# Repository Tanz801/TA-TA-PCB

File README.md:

This is a PCB based on TA-TA from the game Arknight endfields. Designed to be a simple digital pet. This was made for week 1 of hackclub half-life, and I choose to make TA-TA because the beginner project was a digital pet and I just thought TA-TA was a pretty cool and cute character.

## Features

OLED screen for faces
Temperature sensor
Buzzer
Onboard battery charger
IMU to detect movement and orientation.

To be added:
Full organic feeling reactions to external stimuli

## Firmware flashing
The firmware can be flashed by downloading the firmware folder, opening as an esp-idf project, and flashing. However if you don't have the esp-idf framework installed or don't know how to use it, you can use python to flash the precompiled binaries through esptool

1. Install esptool``` pip install esptool ```
2. navigate to TA-TA-Firmware
3. run the following command
```python -m esptool --port PORT --baud 460800 write_flash @build/flashing_args```
replace PORT with the COM number of the esp if you're on windows, or the port on mac or linux.

## Assembling

Components just need to be soldered onto the pcb. The following sections can be done in any order:

### Microcontroller:
The Xiao ESP32 C3 is soldered onto the only component spot with surface mounts, the "pins" of the MCU should match the SMD pads on the PCB and the silkscreen

### Power button:
Solder the push button in the correct orientation based on the silkscreen at SW1, right side of the PCB

### Temperature sensor
Put the THT pins of the TMP36 through the holes next to U1 at the top left of the PCB, and bend it and solder it according to the silk screen.

A 0.1uF ceramic capacitor should be soldered at C1 directly underneath the TMP36

### IMU
If the MPU6050 did not come with header pins, solder headerpins onto the breakout board, make sure the spacers are at the bottom.
Solder the pins to J2 on the left of the microcontroller

### Buzzer
Solder the diode at D1, at the top of the PCB, make sure the direction of the diode (the white line) matches that of the silk screen

The transistor is soldered at the 3 THT holes at Q1, make sure the emitter is soldered to pin 1, the only hole among the 3 with a square pad.

A 1k resistor is soldered at R1, right below the transistor

Finally solder the buzzer at BZ1, with the anode at pin one (the hole with the square pad)

### Battery
the battery shouldn't be soldered but instead secured through any means such as double sided tape.
before connecting the battery to the jst connector, confirm the polarity of the battery, **look from the orientation where the buzzer would be at the top**. If when plugged in, the voltage source is on the right and gnd is on the left, nothing needs to be done, if its the reverse, scratch off the 2 preconnected solder jumpers at the bottom of the PCB then join the 2 previously disconnected jumpers with solder. Now the battery can be safely plugged in.

## BOM

|Item                                      |amount|cost (ea. CAD)|Link                                                                                                                                                                                                                                                                                                                                                                                                                                                                                                                                                                                                                                                                             |
|------------------------------------------|------|--------------|---------------------------------------------------------------------------------------------------------------------------------------------------------------------------------------------------------------------------------------------------------------------------------------------------------------------------------------------------------------------------------------------------------------------------------------------------------------------------------------------------------------------------------------------------------------------------------------------------------------------------------------------------------------------------------|
|XIAO ESP32 C3                             |1     |13.19         |https://www.aliexpress.com/item/1005008791937363.html?spm=a2g0o.productlist.main.1.a1e51039rrC4SW&algo_pvid=b22ce7b4-fbff-4a97-8525-81d1d1d06f15&algo_exp_id=b22ce7b4-fbff-4a97-8525-81d1d1d06f15-0&pdp_ext_f=%7B%22order%22%3A%221499%22%2C%22spu_best_type%22%3A%22price%22%2C%22eval%22%3A%221%22%2C%22fromPage%22%3A%22search%22%7D&pdp_npi=6%40dis%21CAD%2113.19%2113.19%21%21%219.07%219.07%21%402101ef5e17917414181325465e0fbf%2112000052930246748%21sea%21CA%213968153684%21X%211%210%21n_tag%3A-29919%3Bd%3Ab9e668a9%3Bm03_new_user%3A-29895&curPageLogUid=pBK0H0wVxh6J&utparam-url=scene%3Asearch%7Cquery_from%3A%7Cx_object_id%3A1005008791937363%7C_p_origin_prod%3A |
|0.96 OLED                                 |1     |3.86          |https://www.aliexpress.com/item/1005006141235306.html                                                                                                                                                                                                                                                                                                                                                                                                                                                                                                                                                                                                                            |
|MPU6050                                   |1     |3.41          |https://www.aliexpress.com/item/1005008714169630.html                                                                                                                                                                                                                                                                                                                                                                                                                                                                                                                                                                                                                            |
|TMP32 Temperature sensor                  |1     |0.92          |https://www.aliexpress.com/item/4000082221164.html?mp=1                                                                                                                                                                                                                                                                                                                                                                                                                                                                                                                                                                                                                          |
|Passive buzzer                            |1     |0.43          |https://www.aliexpress.com/item/1005006135620280.html?spm=a2g0o.productlist.main.1.73593b6a9n0rFF&algo_pvid=2a9f04ca-f1d5-416f-93e7-f65157e7bf2e&algo_exp_id=2a9f04ca-f1d5-416f-93e7-f65157e7bf2e-0&pdp_ext_f=%7B%22order%22%3A%22151%22%2C%22spu_best_type%22%3A%22price%22%2C%22eval%22%3A%221%22%2C%22fromPage%22%3A%22search%22%7D&pdp_npi=6%40dis%21CAD%216.52%214.25%21%21%2130.05%2119.60%21%402101ea8f17917437858606267e0c2c%2112000035917873697%21sea%21CA%213968153684%21X%211%210%21n_tag%3A-29919%3Bd%3Ab9e668a9%3Bm03_new_user%3A-29895&curPageLogUid=UEYBK5cUuoOp&utparam-url=scene%3Asearch%7Cquery_from%3A%7Cx_object_id%3A1005006135620280%7C_p_origin_prod%3A  |
|2N2222 NPN transistor                     |1     |0.09          |https://www.aliexpress.com/item/1005005776372882.html                                                                                                                                                                                                                                                                                                                                                                                                                                                                                                                                                                                                                            |
|300mAh LiPo Battery 3.7V                  |1     |8.79          |https://www.aliexpress.com/item/1005008218024646.html?spm=a2g0o.productlist.main.3.3e222b94krLFEf&algo_pvid=362b0e01-9ad2-44a0-9ac8-8f41d8200535&algo_exp_id=362b0e01-9ad2-44a0-9ac8-8f41d8200535-2&pdp_ext_f=%7B%22order%22%3A%228081%22%2C%22spu_best_type%22%3A%22price%22%2C%22eval%22%3A%221%22%2C%22fromPage%22%3A%22search%22%7D&pdp_npi=6%40dis%21CAD%2117.95%218.43%21%21%2182.69%2138.86%21%402101d3fe17917661419256252e1338%2112000044269020516%21sea%21CA%213968153684%21X%211%210%21n_tag%3A-29919%3Bd%3Ab9e668a9%3Bm03_new_user%3A-29895&curPageLogUid=c0LEzqcbYYwl&utparam-url=scene%3Asearch%7Cquery_from%3A%7Cx_object_id%3A1005008218024646%7C_p_origin_prod%3A|
|1N4148 Diodes                             |1     |0.02          |https://www.aliexpress.com/item/4001126137167.html?algo_exp_id=5643a195-8cb6-4ff1-847c-ea78bd3a77c7-1&pdp_ext_f=%7B%22order%22%3A%222192%22%2C%22spu_best_type%22%3A%22price%22%2C%22eval%22%3A%221%22%2C%22fromPage%22%3A%22search%22%7D&utparam-url=scene%3Asearch%7Cquery_from%3A%7Cx_object_id%3A4001126137167%7C_p_origin_prod%3A                                                                                                                                                                                                                                                                                                                                           |
|1k resistor                               |1     |0.01          |https://www.aliexpress.com/item/1005006186890215.html?mp=1                                                                                                                                                                                                                                                                                                                                                                                                                                                                                                                                                                                                                       |
| 0.1 µF ceramic capacitor                 |1     |0.02          |https://www.aliexpress.com/item/1005011742959553.html                                                                                                                                                                                                                                                                                                                                                                                                                                                                                                                                                                                                                            |
|JST-PH housing                            |1     |0.03          |https://www.aliexpress.com/item/1005004955655144.html?mp=1                                                                                                                                                                                                                                                                                                                                                                                                                                                                                                                                                                                                                       |
|6x6x5MM 4PIN G90 Tactile Tact Push Button |1     |0.06          |https://www.aliexpress.com/item/32873398324.html?mp=1&pdp_ext_f=%7B%22cart2PdpParams%22%3A%7B%22pdpBusinessMode%22%3A%22retail%22%7D%7D                                                                                                                                                                                                                                                                                                                                                                                                                                                                                                                                          |
|PCB                                       |1     |2.56          |https://cart.jlcpcb.com/quote?rand=0.883814583740498                                                                                                                                                                                                                                                                                                                                                                                                                                                                                                                                                                                                                             |
|Total                                     |      |33.39         |                     

## PCB Wiring and Schematics

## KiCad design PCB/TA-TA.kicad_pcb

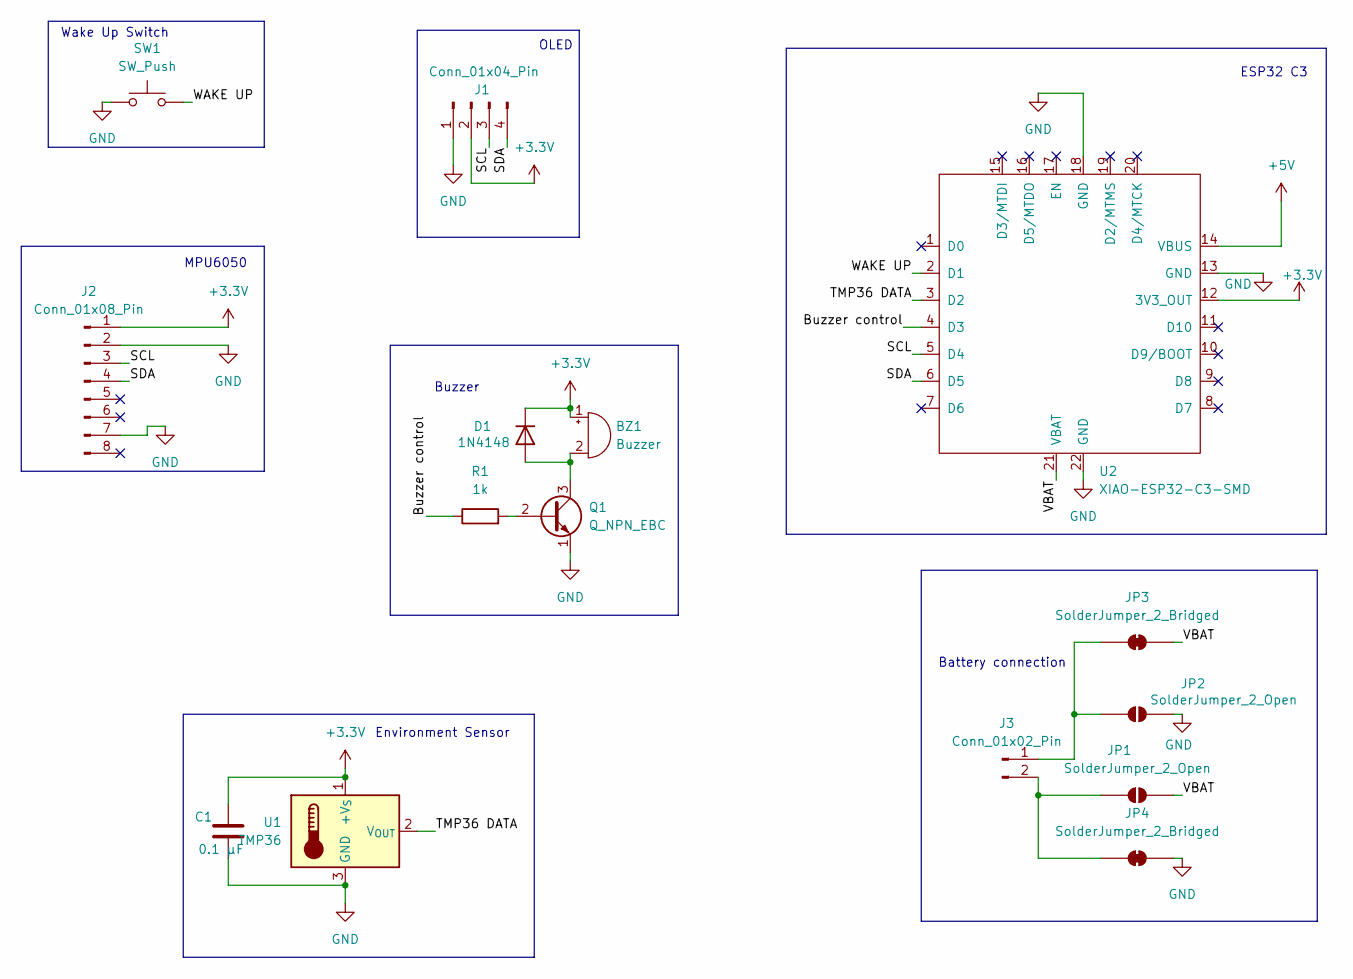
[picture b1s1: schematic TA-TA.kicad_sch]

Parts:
BZ1: Buzzer; Buzzer_12x9.5RM7.6
C1: 0.1 µF; C_Disc_D5.0mm_W2.5mm_P2.50mm
D1: 1N4148; D_DO-35_SOD27_P7.62mm_Horizontal
J1: Conn_01x04_Pin; Display_128x64_096_I2C
J2: Conn_01x08_Pin; MPU6050_Module
J3: Conn_01x02_Pin; JST_PH_S2B-PH-K_1x02_P2.00mm_Horizontal
JP1, JP2: SolderJumper_2_Open; SolderJumper-2_P1.3mm_Open_RoundedPad1.0x1.5mm
JP3, JP4: SolderJumper_2_Bridged; SolderJumper-2_P1.3mm_Bridged_RoundedPad1.0x1.5mm
Q1: Q_NPN_EBC; TO-92_Inline_W4.0mm_Horizontal_FlatSideDown
R1: 1k; R_Axial_DIN0207_L6.3mm_D2.5mm_P10.16mm_Horizontal
SW1: SW_Push; SW_PUSH_6mm
U1: TMP36; TO-92_W4.0mm_StaggerEven_Horizontal_FlatSideDown
U2: XIAO-ESP32-C3-SMD

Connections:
+3.3V: BZ1.1 (+), C1.1, D1.1 (K), J1.2, J2.1, U1.1 (+V_{S}), U2.12 (3V3_OUT)
+5V: U2.14 (VBUS)
/Buzzer control: R1.1, U2.4 (D3)
/SCL: J1.3, J2.3, U2.5 (D4)
/SDA: J1.4, J2.4, U2.6 (D5)
/TMP36 DATA: U1.2 (V_{OUT}), U2.3 (D2)
/VBAT: JP1.2 (B), JP3.2 (B), U2.21 (VBAT)
/WAKE UP: SW1.2, U2.2 (D1)
GND: C1.2, J1.1, J2.2, J2.7, JP2.2 (B), JP4.2 (B), Q1.1 (E), SW1.1, U1.3 (GND), U2.13 (GND), U2.18 (GND), U2.22 (GND)
unnamed: BZ1.2 (-), D1.2 (A), Q1.3 (C)
unnamed: J3.1, JP2.1 (A), JP3.1 (A)
unnamed: J3.2, JP1.1 (A), JP4.1 (A)
unnamed: Q1.2 (B), R1.2

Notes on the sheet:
Environment Sensor
ESP32 C3
OLED
Battery connection
Wake Up Switch
Buzzer
MPU6050

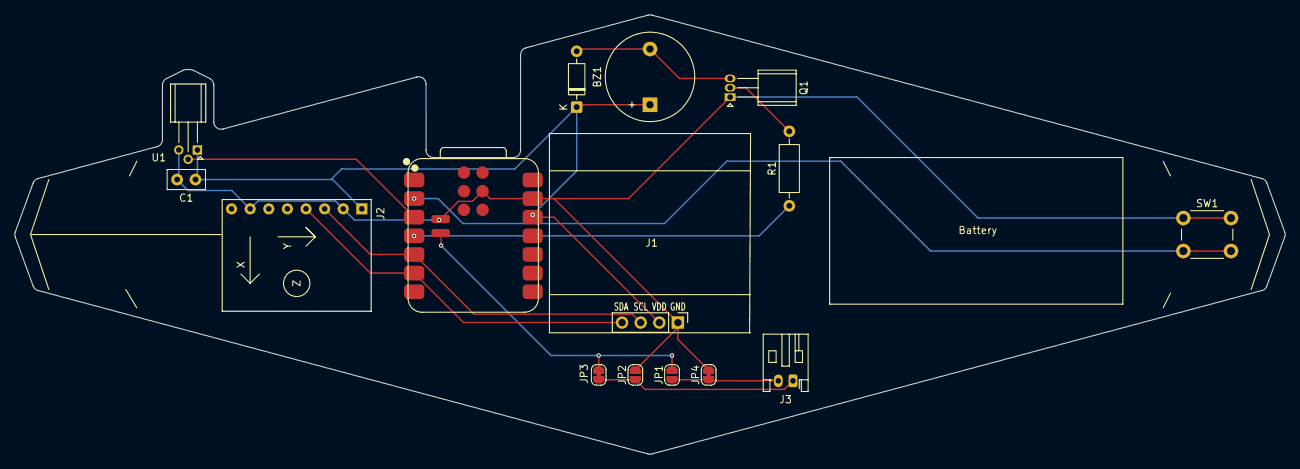
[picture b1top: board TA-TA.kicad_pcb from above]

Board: 2 copper layers, 173.3 x 59.9 mm, 15 parts (0 on the bottom side), 12 nets.
